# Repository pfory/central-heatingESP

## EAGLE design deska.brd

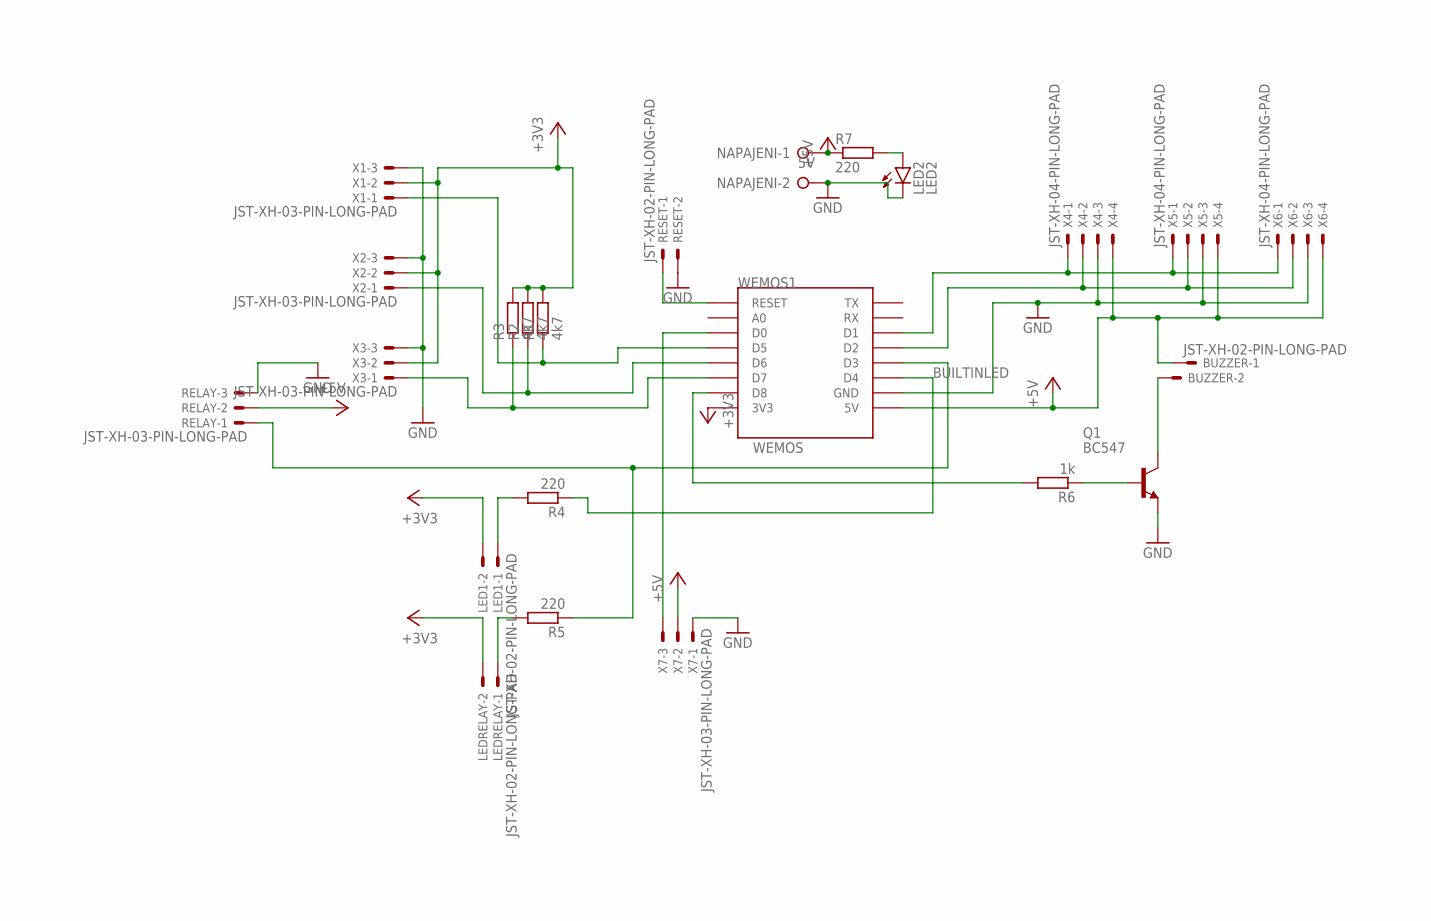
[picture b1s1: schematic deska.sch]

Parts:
BUZZER: JST-XH-02-PIN-LONG-PAD; JST-XH-02-PACKAGE-LONG-PAD
LED1: JST-XH-02-PIN-LONG-PAD; JST-XH-02-PACKAGE-LONG-PAD
LED2: LED2; LED3MM
LEDRELAY: JST-XH-02-PIN-LONG-PAD; JST-XH-02-PACKAGE-LONG-PAD
NAPAJENI: 5V; W237-132
Q1: BC547; TO92
R1, R2, R3: 4k7; 0207/7
R4, R5, R7: 220; 0207/7
R6: 1k; 0207/7
RELAY: JST-XH-03-PIN-LONG-PAD; JST-XH-03-PACKAGE-LONG-PAD
RESET: JST-XH-02-PIN-LONG-PAD; JST-XH-02-PACKAGE-LONG-PAD
WEMOS1: WEMOS; WEMOS-D1-MINI
X1, X2, X3, X7: JST-XH-03-PIN-LONG-PAD; JST-XH-03-PACKAGE-LONG-PAD
X4, X5, X6: JST-XH-04-PIN-LONG-PAD; JST-XH-04-PACKAGE-LONG-PAD

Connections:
+3V3: LED1.2, LEDRELAY.2, R1.2, R2.2, R3.2, WEMOS1.3V3, X1.2, X2.2, X3.2
+5V: BUZZER.1, NAPAJENI.1, R7.1, RELAY.2, WEMOS1.5V, X4.4, X5.4, X6.4, X7.2
BUILTINLED: R4.1, WEMOS1.D4
GND: LED2.K (C), NAPAJENI.2, Q1.1 (E), RELAY.3, RESET.2, WEMOS1.GND, X1.3, X2.3, X3.3, X4.3, X5.3, X6.3, X7.1
unnamed: R1.1, WEMOS1.D5, X1.1
unnamed: LEDRELAY.1, R5.2
unnamed: LED2.A, R7.2
unnamed: RESET.1, WEMOS1.RESET
unnamed: LED1.1, R4.2
unnamed: Q1.2 (B), R6.1
unnamed: R6.2, WEMOS1.D8
unnamed: R3.1, WEMOS1.D7, X3.1
unnamed: WEMOS1.D0, X7.3
unnamed: WEMOS1.D1, X4.1, X5.1, X6.1
unnamed: WEMOS1.D2, X4.2, X5.2, X6.2
unnamed: R5.1, RELAY.1, WEMOS1.D3
unnamed: BUZZER.2, Q1.3 (C)
unnamed: R2.1, WEMOS1.D6, X2.1

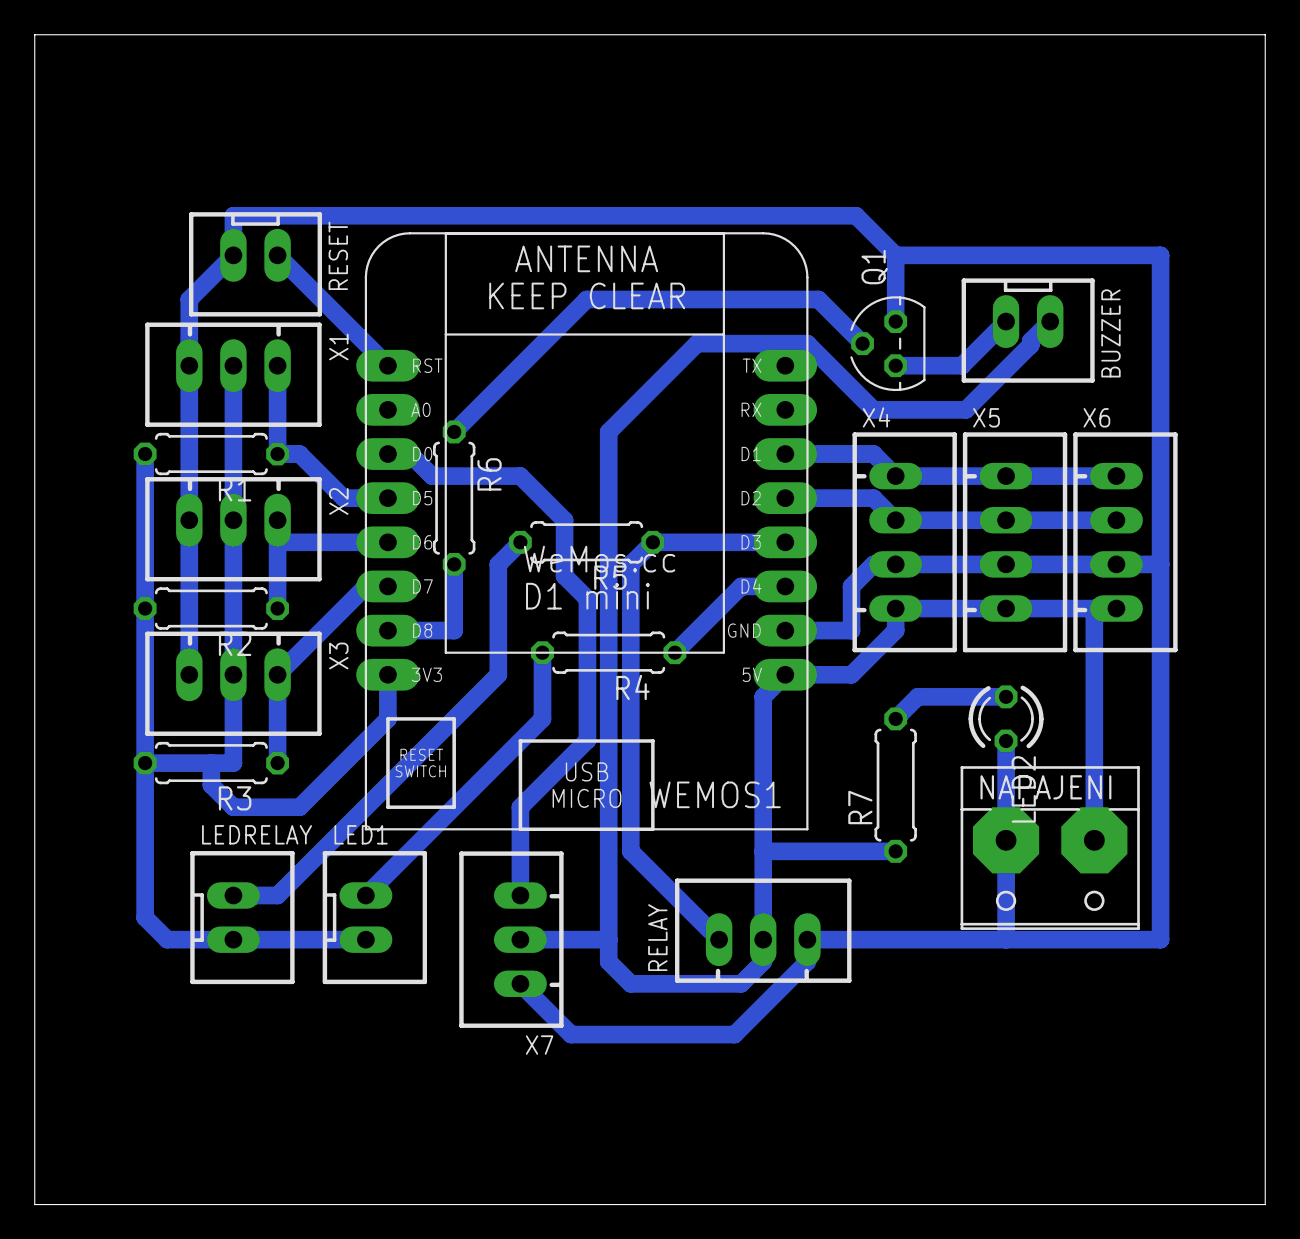
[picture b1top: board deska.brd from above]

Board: 2 copper layers, 70.8 x 67.3 mm, 23 parts (0 on the bottom side), 18 nets.

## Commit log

2018-10-08 init
2018-10-15 nastaveni teplot
2018-10-17 deska wemos lib
2019-02-20 upravy desky
2019-02-21 initESP
2019-09-24 změna na JST XH konektory
2019-09-24 pridana ledka konektory
2019-10-02 upravy kodu
2019-10-02 deska
2019-10-02 0.93
2019-10-03 +konfiguracni soubor
2019-10-03 +reset pin na desku +popis pinu
2019-10-03 nacitani a ukladan konfigurace do souboru
2019-10-04 staus LED na D8 pir pin na D4
2019-10-04 deska s prohozením pinů
2019-10-05 nulovani statistik o pulnoci
2019-10-05 rozpinani rele na zaklade teplotni diference
2019-10-05 oprava predchozich 2 commitu
2019-10-05 a jetse jedna chybka
2019-10-09 upravy mqtt promennych
2019-10-09 zjednoduseni kodu
2019-10-16 1.00
2019-10-30 vyhazeni nepotrebne funkcionality pri chybe meridel in a out spusti cerpadlo kvuli bezpecnosti
2019-10-30 1.03
2019-11-25 definice PIR
2019-11-26 +ota
2019-12-18 1.05 PIR
2020-01-20 + vyrobene desky
2020-01-21 + mqtt setup
2020-01-22 ventil 1 funkcni
2020-01-23 parametrizace ventilu
2020-04-03 ovladani ventilu z nodered
2020-07-22 kosmetika
2020-09-19 + double reset detector + timeouty pro config portal
2020-12-10 1.20 - prekopano sitovani aby nevadil vypadek routeru
2020-12-10 vypnuto simtemp
2020-12-11 oprava chyby s teplomery
2020-12-17 odstraneni duplicit v include
2021-12-07 1.20
2021-12-08 +lwt rezim online/offline
2021-12-08 1.31 + posilani teplot tempON a tempDiff
2021-12-08 v1.32
2021-12-13 1.36
2021-12-16 +timer pro reconnect
2023-10-10 nove fce.h
2023-10-24 -ventily
2023-11-25 zmena posilani dat na 15sec
2023-11-27 uprava blikani teckami
2023-12-19 revize
2024-01-31 lokalni time server
2024-02-29 shořel PIR sensor
2025-02-24 oprava zobrazovani stavu termohlavice a pridani stavu vytezovace
2025-02-24 oprava warningu
2025-05-20 měření teplot
